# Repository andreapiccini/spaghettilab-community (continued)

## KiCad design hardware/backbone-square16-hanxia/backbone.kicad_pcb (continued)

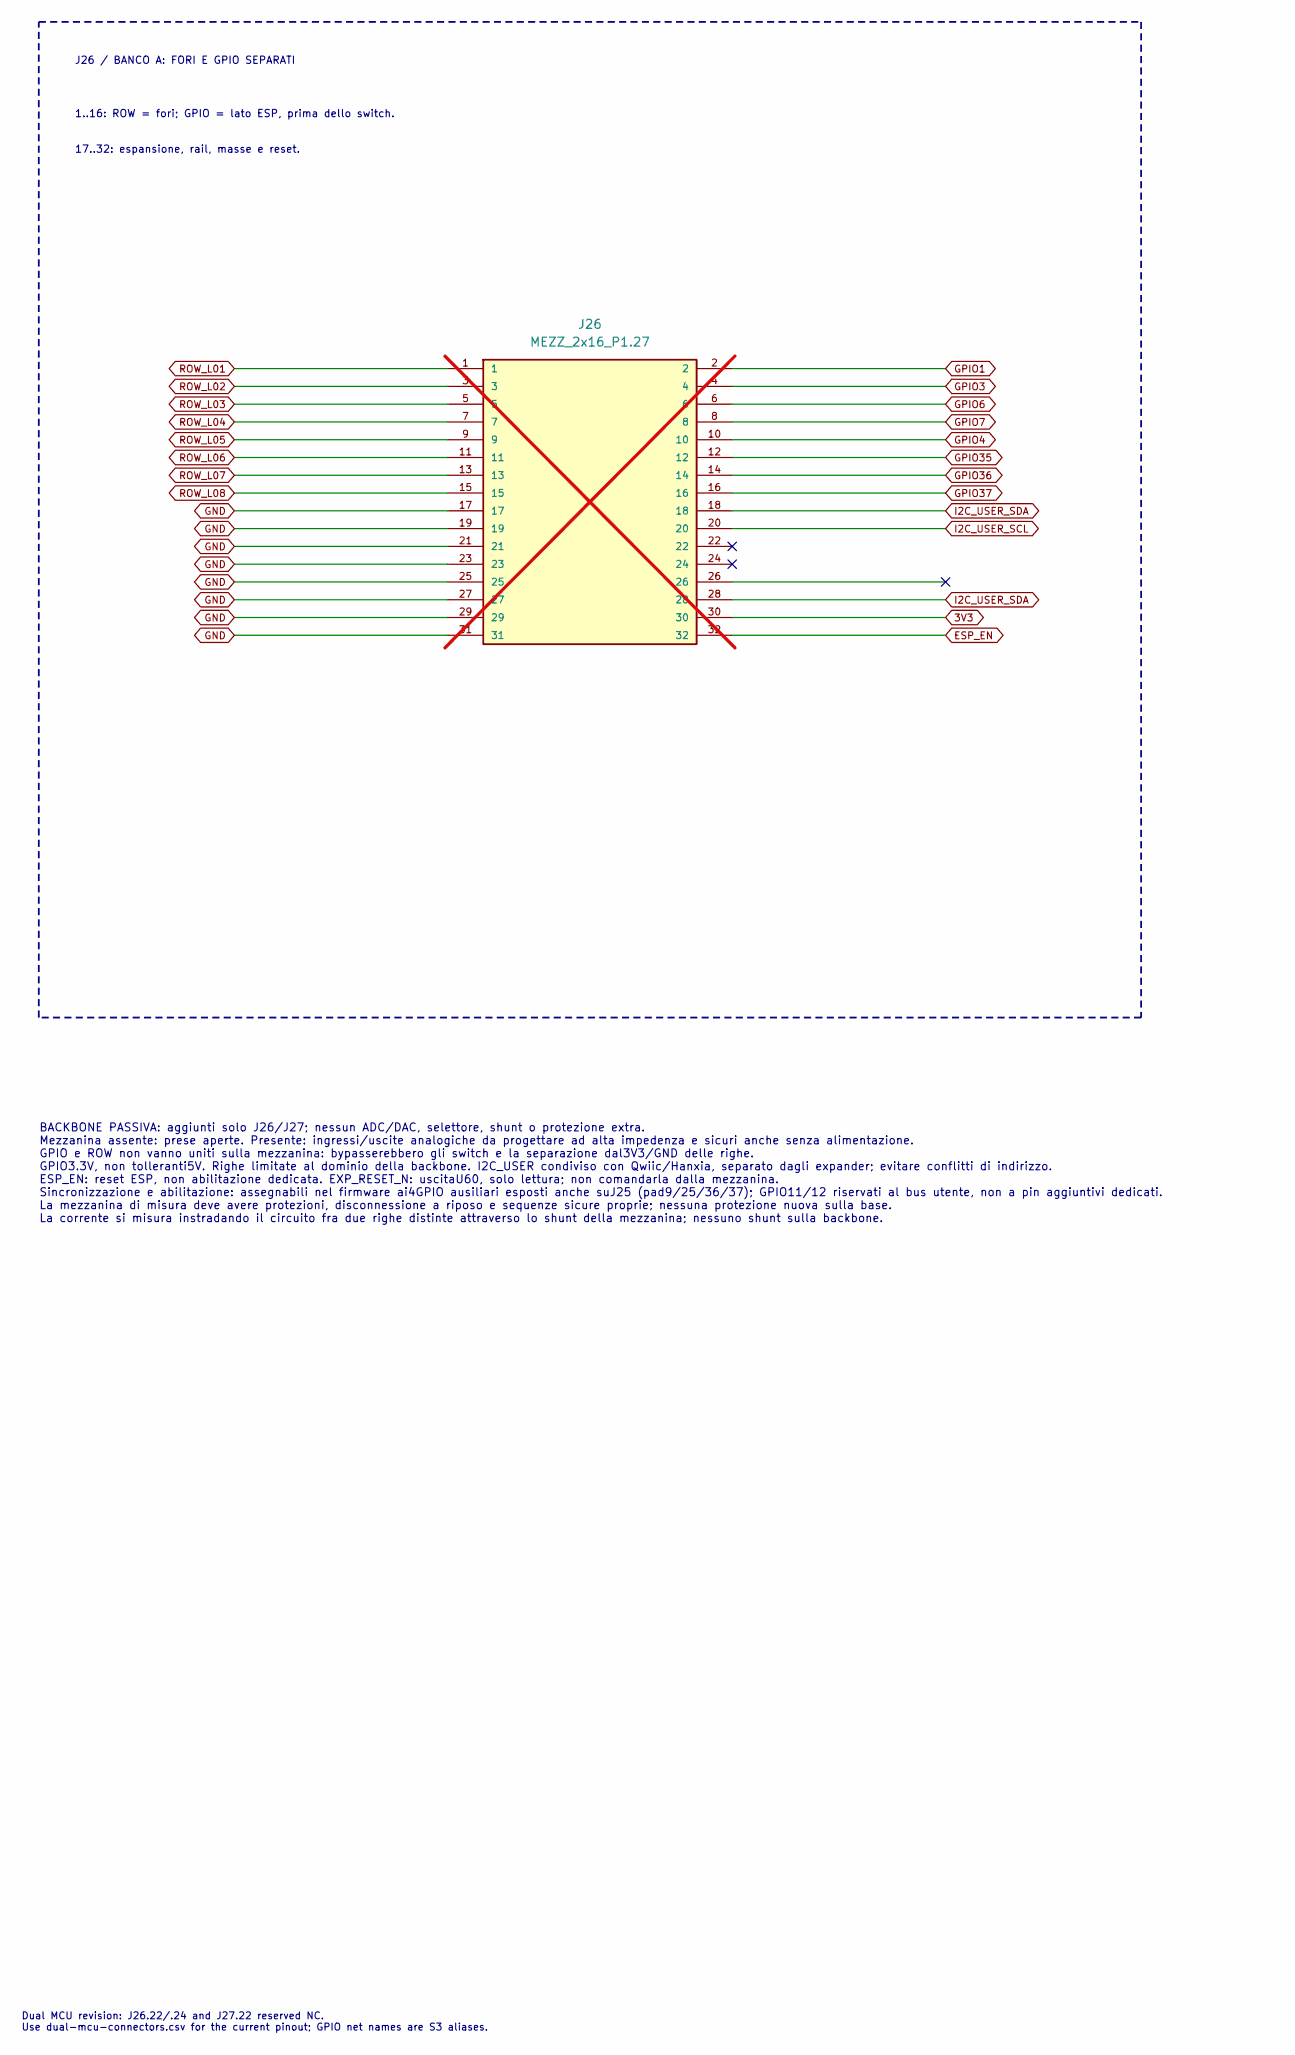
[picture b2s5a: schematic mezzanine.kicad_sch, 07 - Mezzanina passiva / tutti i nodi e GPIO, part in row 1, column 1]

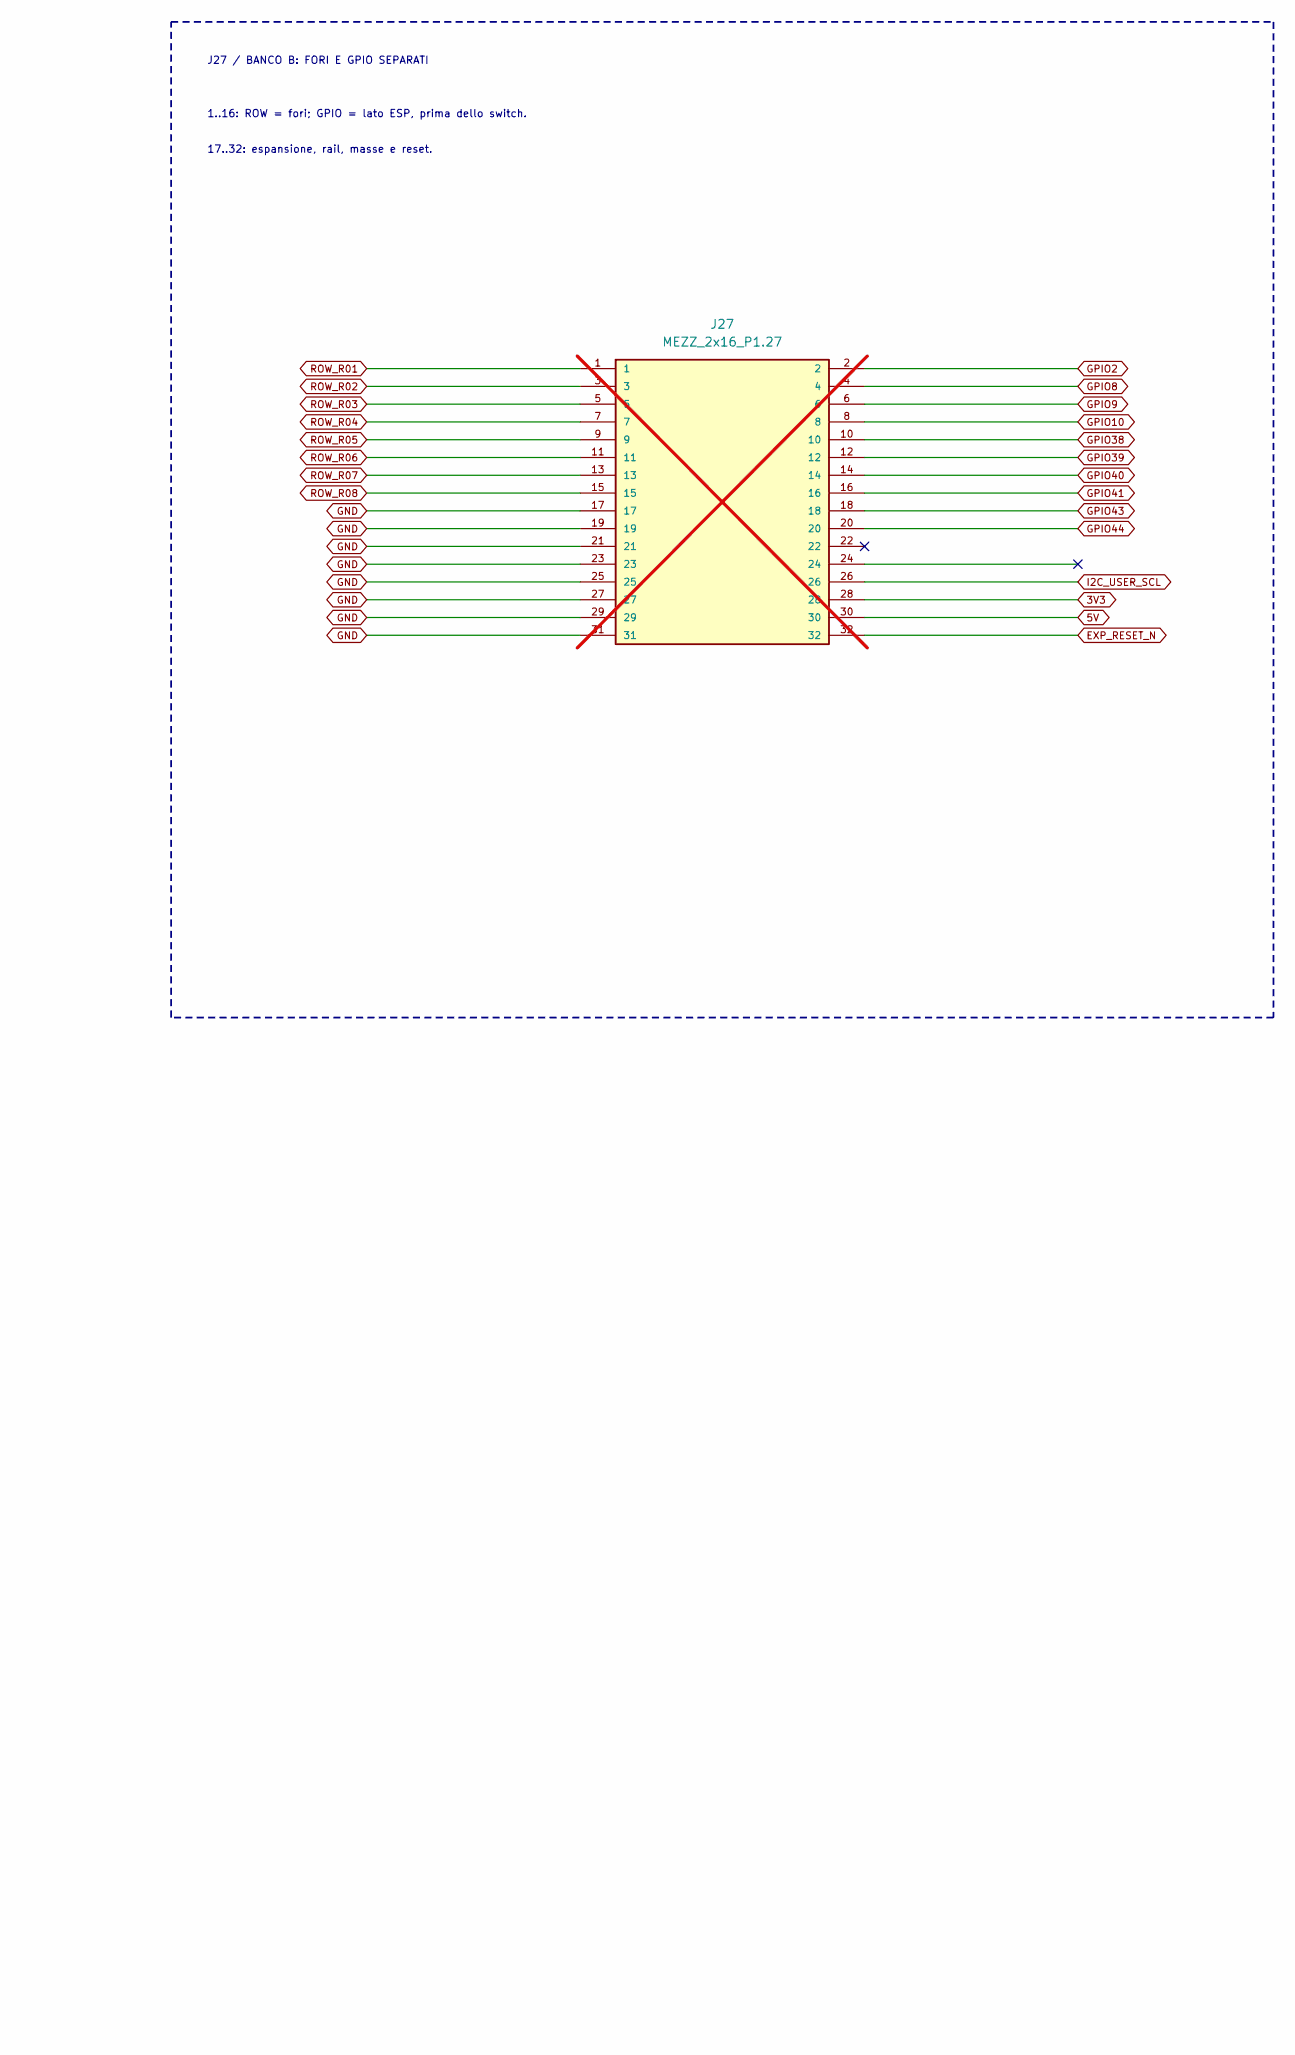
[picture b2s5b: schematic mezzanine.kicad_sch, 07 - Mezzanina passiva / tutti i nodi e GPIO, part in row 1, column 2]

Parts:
J26, J27: MEZZ_2x16_P1.27; PinSocket_2x16_P1.27mm_Vertical; not fitted

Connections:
3V3: J26.30, J27.28; also elsewhere on the board
5V: J27.30; also elsewhere on the board
ESP_EN: J26.32; also elsewhere on the board
EXP_RESET_N: J27.32; also elsewhere on the board
GND: J26.17, J26.19, J26.21, J26.23, J26.25, J26.27, J26.29, J26.31, J27.17, J27.19, J27.21, J27.23, J27.25, J27.27, J27.29, J27.31; also elsewhere on the board
GPIO1: J26.2; also elsewhere on the board
GPIO2: J27.2; also elsewhere on the board
GPIO3: J26.4; also elsewhere on the board
GPIO4: J26.10; also elsewhere on the board
GPIO6: J26.6; also elsewhere on the board
GPIO7: J26.8; also elsewhere on the board
GPIO8: J27.4; also elsewhere on the board
GPIO9: J27.6; also elsewhere on the board
GPIO10: J27.8; also elsewhere on the board
GPIO35: J26.12; also elsewhere on the board
GPIO36: J26.14; also elsewhere on the board
GPIO37: J26.16; also elsewhere on the board
GPIO38: J27.10; also elsewhere on the board
GPIO39: J27.12; also elsewhere on the board
GPIO40: J27.14; also elsewhere on the board
GPIO41: J27.16; also elsewhere on the board
GPIO43: J27.18; also elsewhere on the board
GPIO44: J27.20; also elsewhere on the board
I2C_USER_SCL: J26.20, J27.26; also elsewhere on the board
I2C_USER_SDA: J26.18, J26.28; also elsewhere on the board
ROW_L01: J26.1; also elsewhere on the board
ROW_L02: J26.3; also elsewhere on the board
ROW_L03: J26.5; also elsewhere on the board
ROW_L04: J26.7; also elsewhere on the board
ROW_L05: J26.9; also elsewhere on the board
ROW_L06: J26.11; also elsewhere on the board
ROW_L07: J26.13; also elsewhere on the board
ROW_L08: J26.15; also elsewhere on the board
ROW_R01: J27.1; also elsewhere on the board
ROW_R02: J27.3; also elsewhere on the board
ROW_R03: J27.5; also elsewhere on the board
ROW_R04: J27.7; also elsewhere on the board
ROW_R05: J27.9; also elsewhere on the board
ROW_R06: J27.11; also elsewhere on the board
ROW_R07: J27.13; also elsewhere on the board
ROW_R08: J27.15; also elsewhere on the board

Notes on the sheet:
J26 / BANCO A: FORI E GPIO SEPARATI
1..16: ROW = fori; GPIO = lato ESP, prima dello switch.
17..32: espansione, rail, masse e reset.
J27 / BANCO B: FORI E GPIO SEPARATI
BACKBONE PASSIVA: aggiunti solo J26/J27; nessun ADC/DAC, selettore, shunt o protezione extra. Mezzanina assente: prese aperte. Presente: ingressi/uscite analogiche da progettare ad alta impedenza e sicuri anche senza alimentazione. GPIO e ROW non vanno uniti sulla mezzanina: bypasserebbero gli swit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
Dual MCU revision: J26.22/.24 and J27.22 reserved NC. Use dual-mcu-connectors.csv for the current pinout; GPIO net names are S3 aliases.

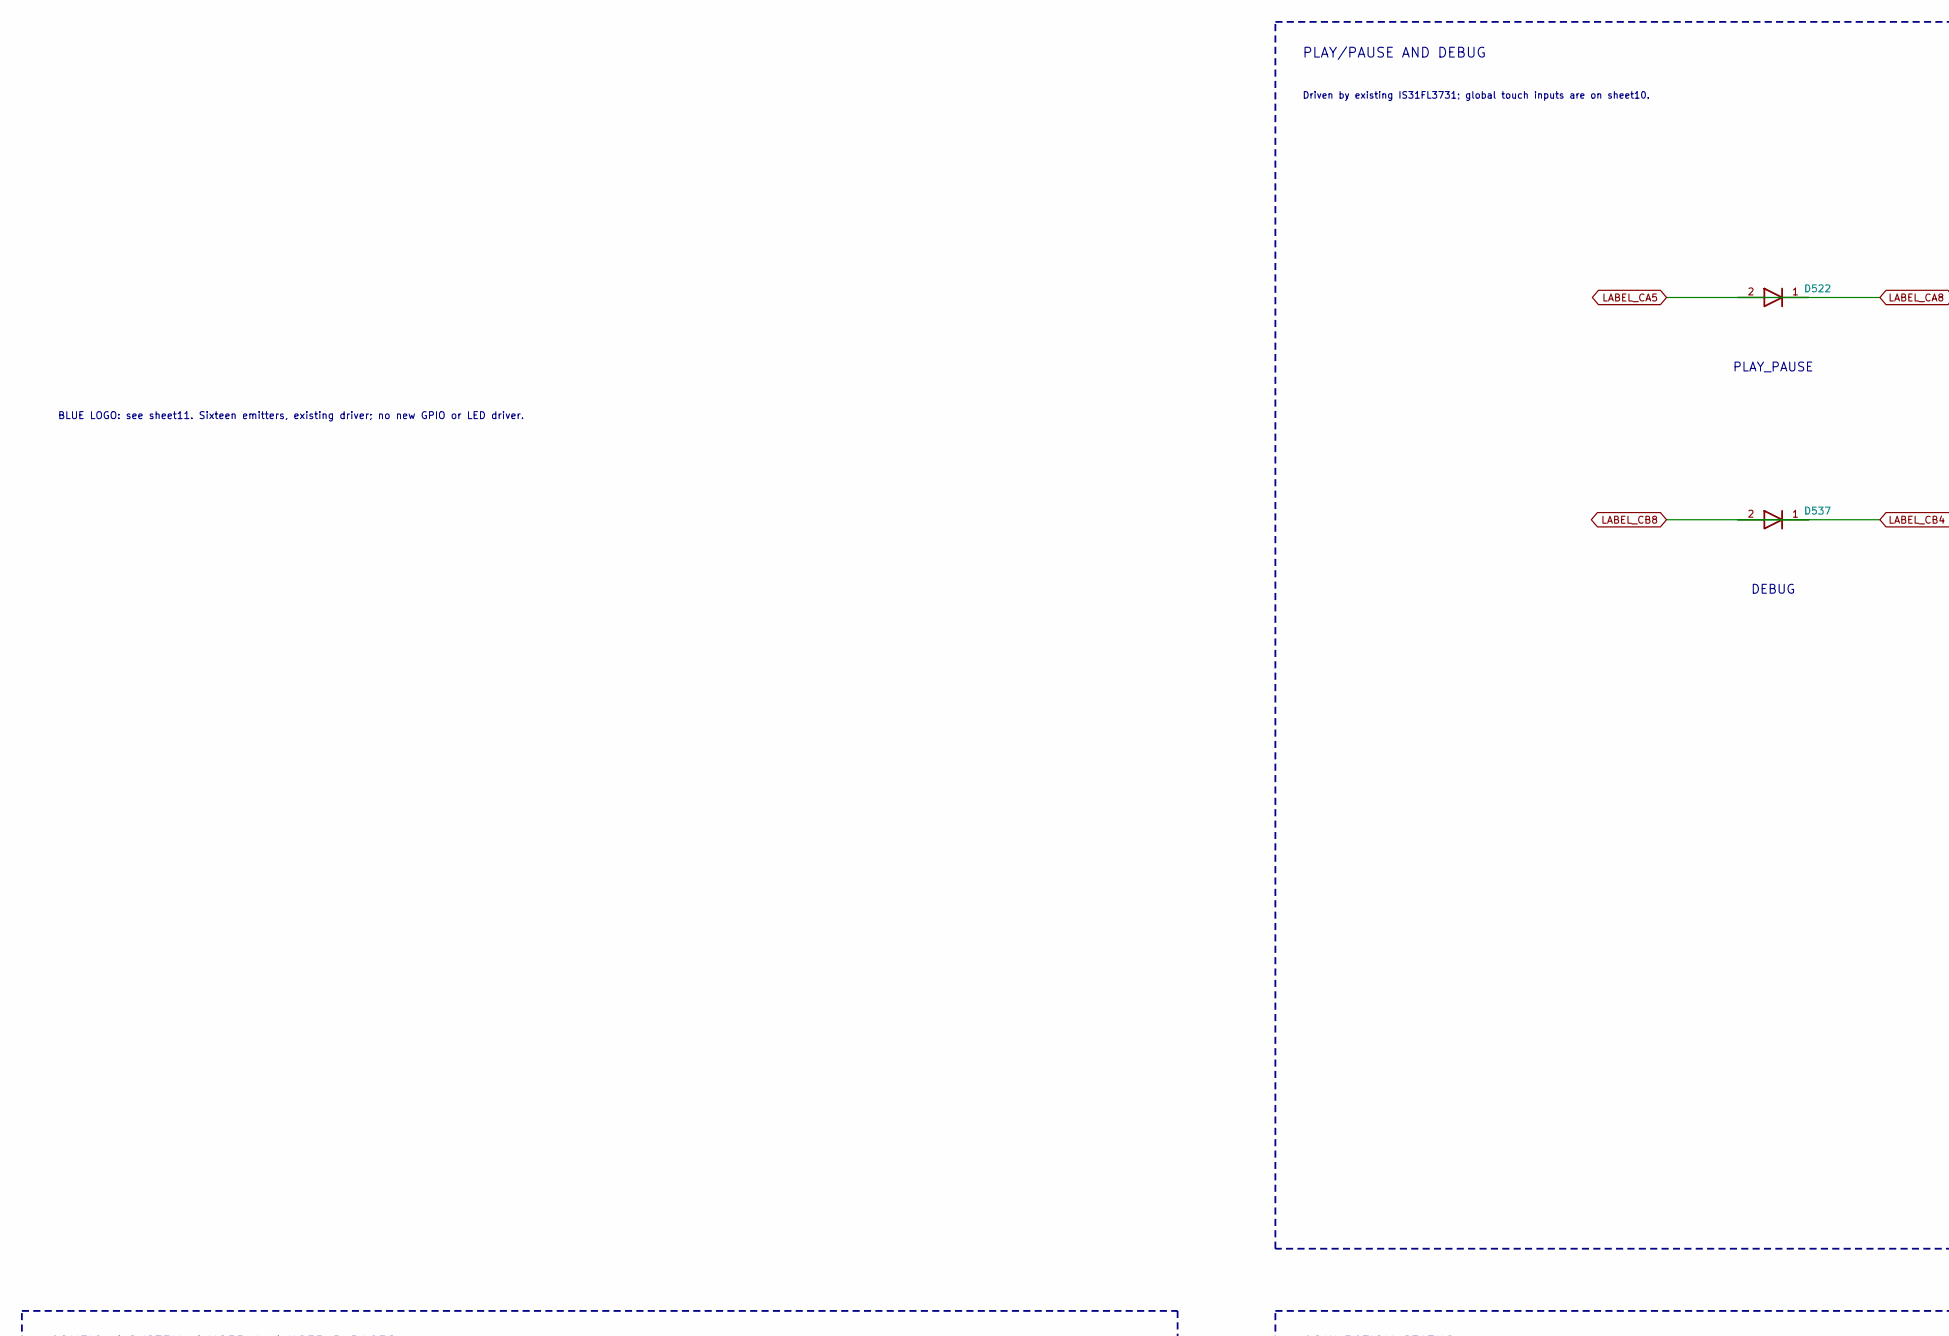
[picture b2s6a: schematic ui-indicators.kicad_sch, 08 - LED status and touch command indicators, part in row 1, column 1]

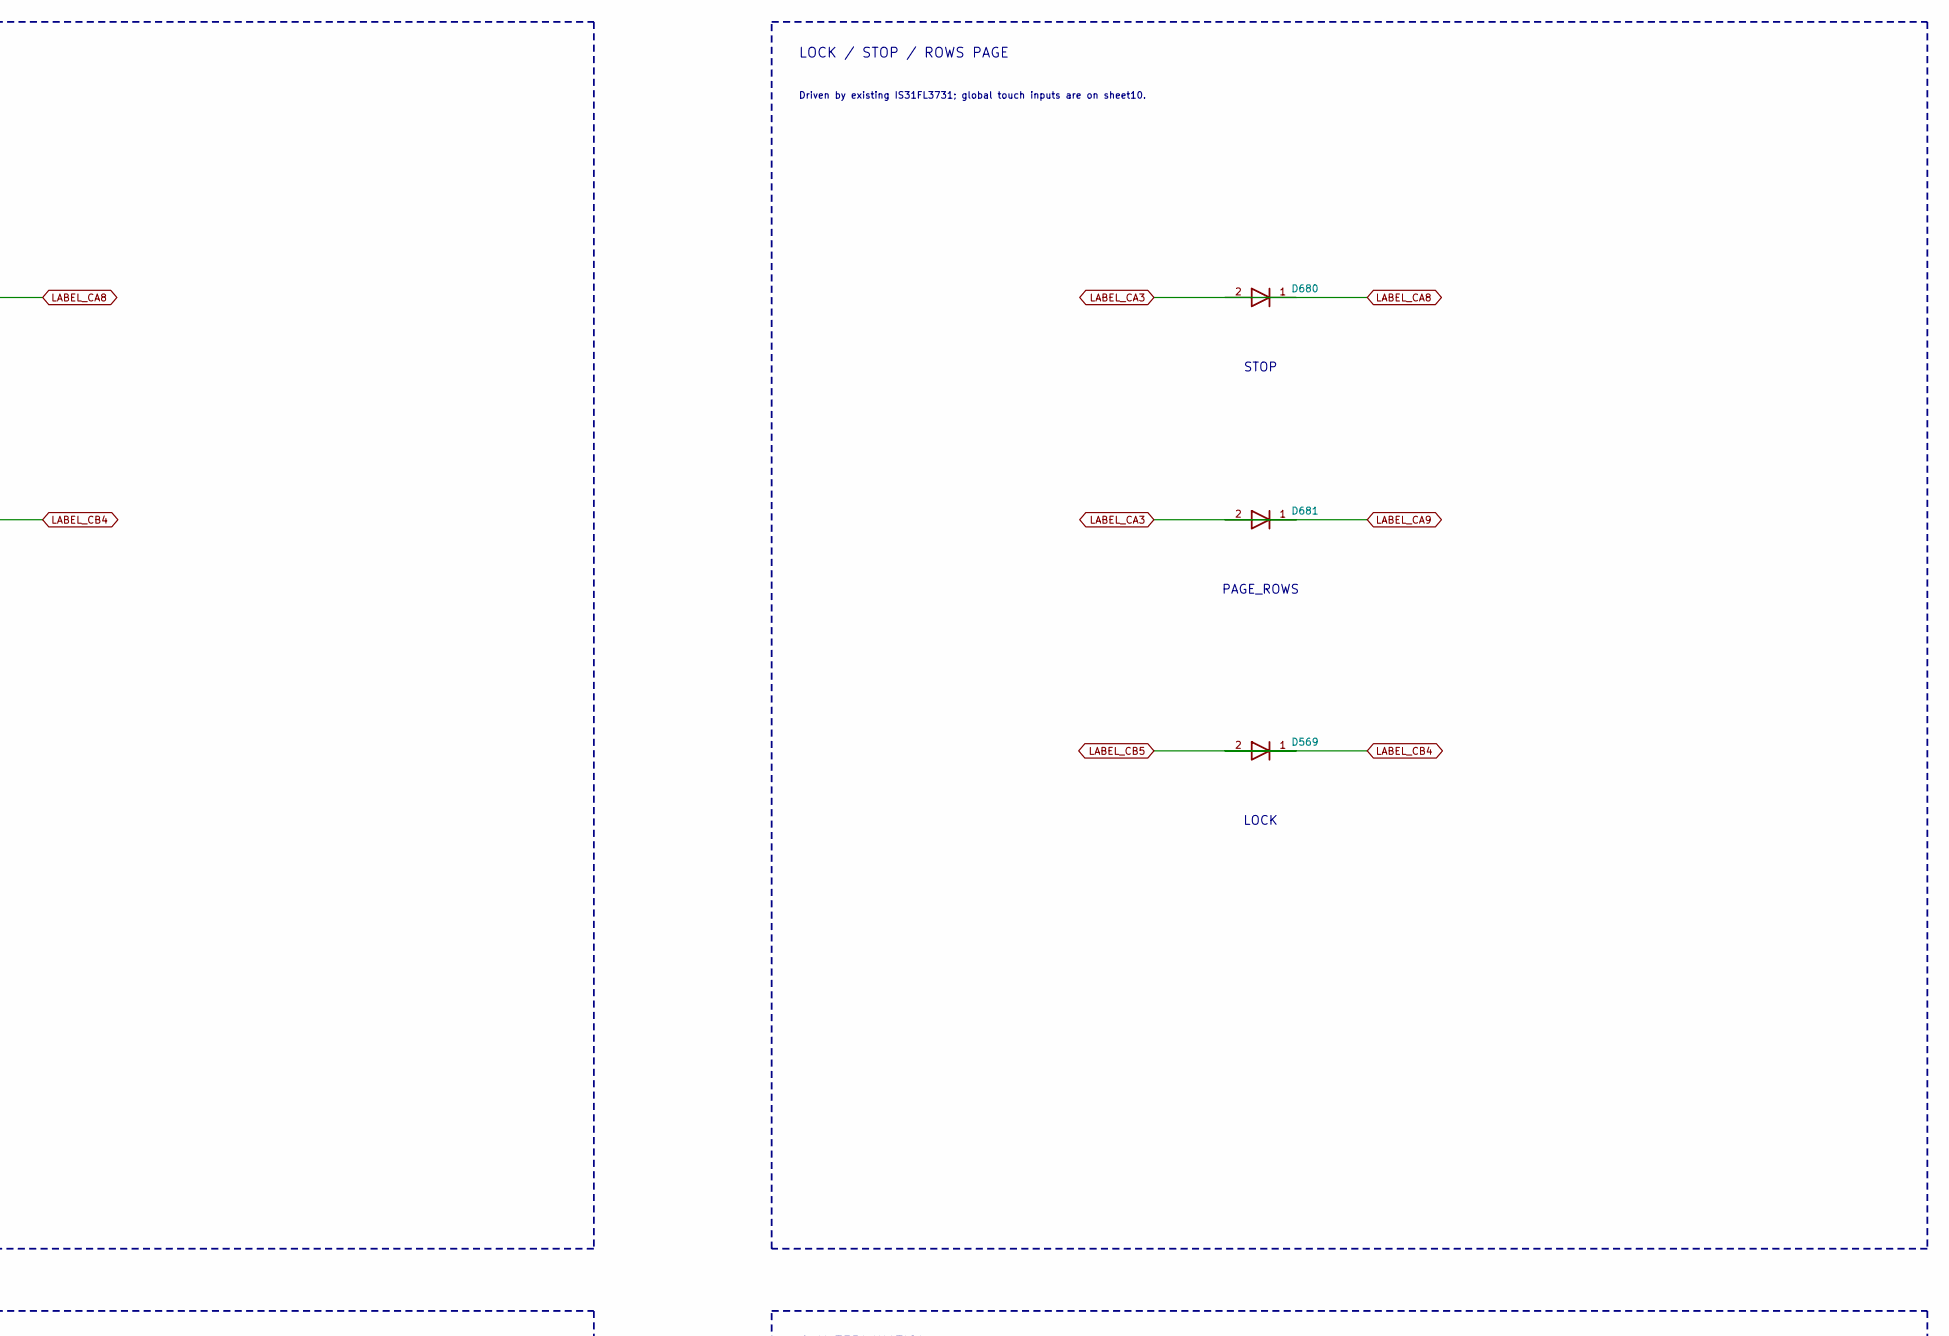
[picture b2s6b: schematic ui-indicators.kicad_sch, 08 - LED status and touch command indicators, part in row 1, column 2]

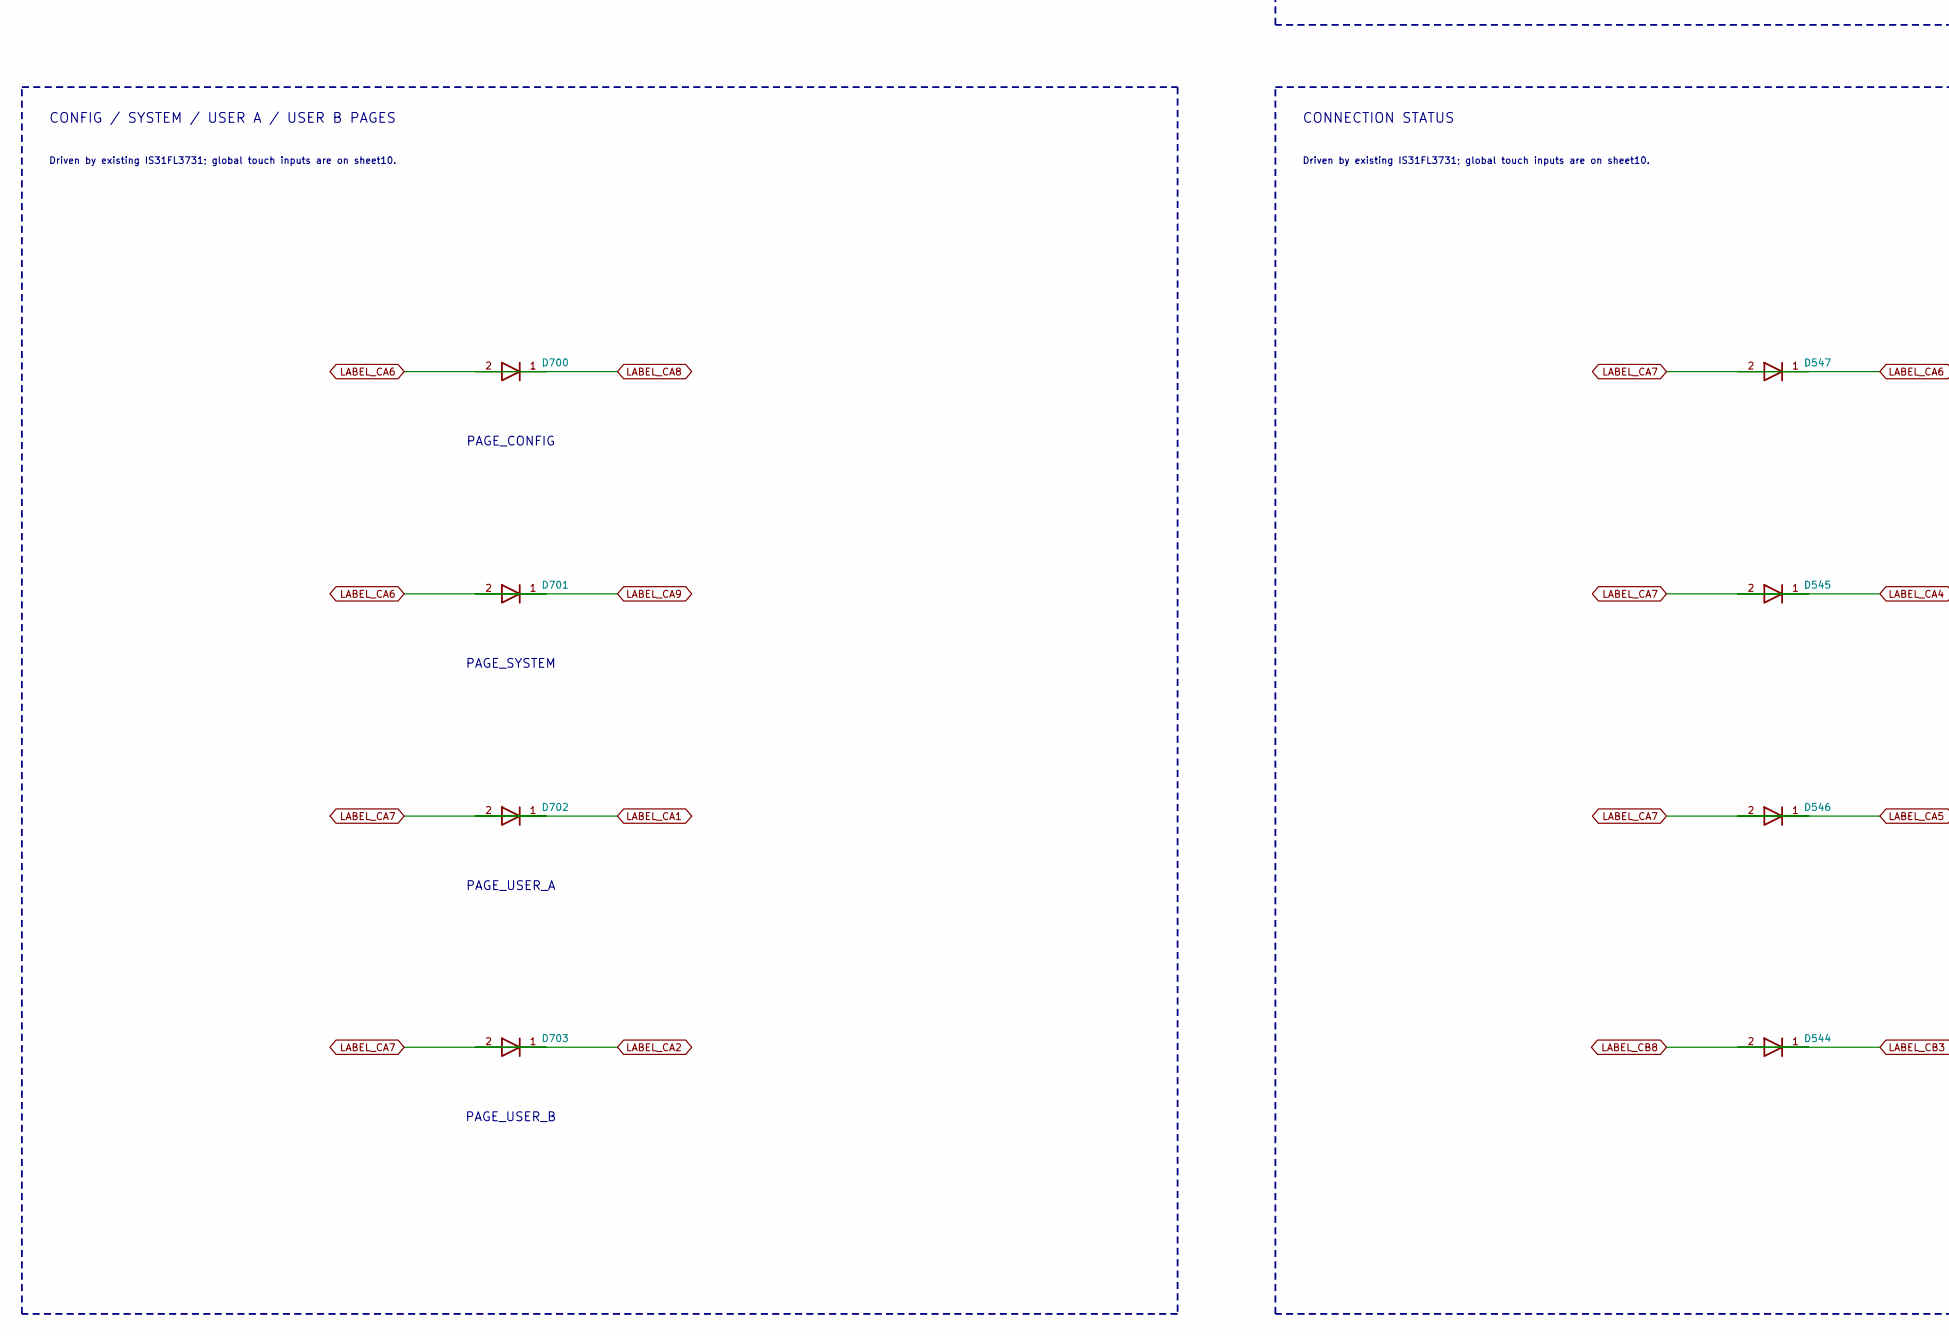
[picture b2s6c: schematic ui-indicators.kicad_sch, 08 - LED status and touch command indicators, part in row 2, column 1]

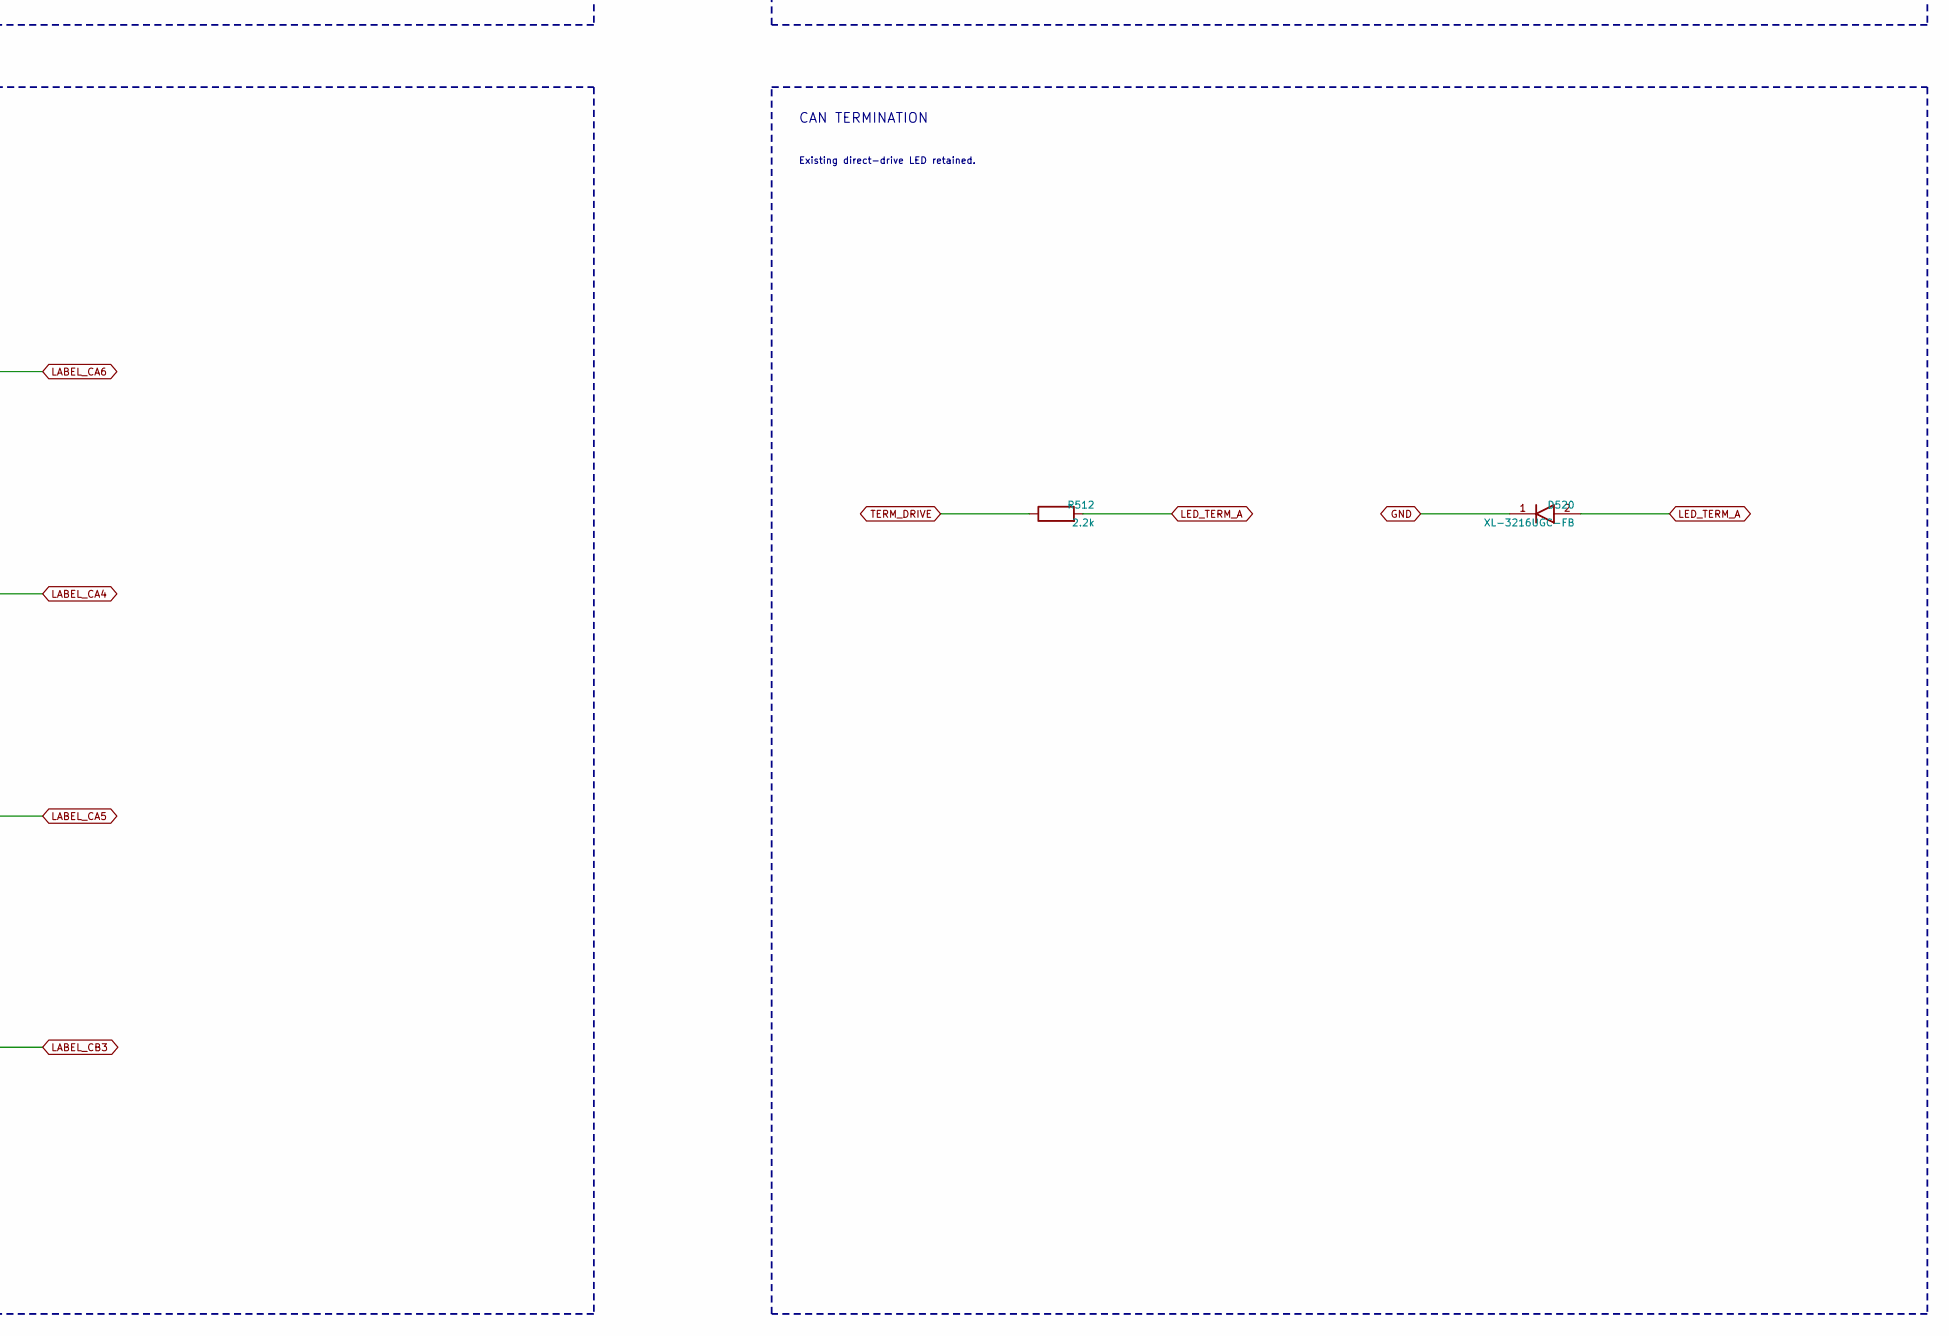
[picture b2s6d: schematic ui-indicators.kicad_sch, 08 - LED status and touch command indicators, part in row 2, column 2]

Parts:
D520, D522, D537, D544, D545: XL-3216UGC-FB; XINGLIGHT_XL3216_Reverse_Word_Window; MPN XL-3216UGC-FB; LCSC Part C3646937
D546, D547: XL-3216UBC-FB; XINGLIGHT_XL3216_Reverse_Word_Window; MPN XL-3216UBC-FB; LCSC Part C3646941
D569: XL-3216SURC-FB; XINGLIGHT_XL3216_Reverse_Word_Window; MPN XL-3216SURC-FB; LCSC Part C3646938
D680, D700, D701, D702, D703: XL-3216UGC-FB; XINGLIGHT_XL3216_Reverse_Word_Window
D681: XL-3216UBC-FB; XINGLIGHT_XL3216_Reverse_Word_Window
R512: 2.2k; R_0603_1608Metric; MPN 0603WAF2201T5E; LCSC Part C4190

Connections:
GND: D520.1 (K); also elsewhere on the board
LABEL_CA1: D702.2 (A); also elsewhere on the board
LABEL_CA2: D703.2 (A); also elsewhere on the board
LABEL_CA3: D680.1 (K), D681.1 (K); also elsewhere on the board
LABEL_CA4: D545.2 (A); also elsewhere on the board
LABEL_CA5: D522.1 (K), D546.2 (A); also elsewhere on the board
LABEL_CA6: D547.2 (A), D700.1 (K), D701.1 (K); also elsewhere on the board
LABEL_CA7: D545.1 (K), D546.1 (K), D547.1 (K), D702.1 (K), D703.1 (K); also elsewhere on the board
LABEL_CA8: D522.2 (A), D680.2 (A), D700.2 (A); also elsewhere on the board
LABEL_CA9: D681.2 (A), D701.2 (A); also elsewhere on the board
LABEL_CB3: D544.2 (A); also elsewhere on the board
LABEL_CB4: D537.2 (A), D569.2 (A); also elsewhere on the board
LABEL_CB5: D569.1 (K); also elsewhere on the board
LABEL_CB8: D537.1 (K), D544.1 (K); also elsewhere on the board
LED_TERM_A: D520.2 (A), R512.2
TERM_DRIVE: R512.1; also elsewhere on the board

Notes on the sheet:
PLAY/PAUSE AND DEBUG
Driven by existing IS31FL3731; global touch inputs are on sheet10.
LOCK / STOP / ROWS PAGE
CONFIG / SYSTEM / USER A / USER B PAGES
CONNECTION STATUS
CAN TERMINATION
Existing direct-drive LED retained.
BLUE LOGO: see sheet11. Sixteen emitters, existing driver; no new GPIO or LED driver.
PLAY_PAUSE
DEBUG
STOP
PAGE_ROWS
LOCK
PAGE_CONFIG
PAGE_SYSTEM
PAGE_USER_A
PAGE_USER_B

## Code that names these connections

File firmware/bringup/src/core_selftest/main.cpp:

#include <Arduino.h>
#include <WiFi.h>
#include <BLEDevice.h>
#include <BLEServer.h>
#include <esp_chip_info.h>
#include <esp_flash.h>
#include <esp_mac.h>

#include "sk6812_rmt.h"

// Pin map from hardware/core/core.kicad_sch + core.kicad_pcb (U19 ESP32-S3-MINI-1).
// USB_D+/D- = GPIO20/19 (native CDC). LED_DATA = GPIO34 via SN74AHCT1G14 (invert!).
// CAN: GPIO5 = CORE_CAN_TX -> SN65HVD230 D, GPIO4 = CORE_CAN_RX <- R (local echo).
// SW2 BOOT = GPIO0. PROG J17 = GPIO43 TX / GPIO44 RX. Link Bay J8 = GPIO35..42,45..48.

static const int kLedGpio = 34;
static const int kCanRx = 4;
static const int kCanTx = 5;
static const int kBoot = 0;
static const int kBayGpios[] = {35, 36, 37, 38, 39, 40, 41, 42, 45, 46, 47, 48};

static bool s_ble_ok = false;

static void banner() {
    Serial.println();
    Serial.println("================================================");
    Serial.println("  SpaghettiLAB CORE  ESP32-S3 self-test");
    Serial.println("  Schematic: hardware/core/core.kicad_sch");
    Serial.println("================================================");
    Serial.println("Commands:  a=all  r=rgb  c=can  w=wifi  b=ble  g=gpio  h=help");
}

static void test_chip() {
    Serial.println();
    Serial.println("[1] Chip / flash / USB");
    Serial.printf("    model     %s  rev %d  cores %d\n", ESP.getChipModel(), ESP.getChipRevision(), ESP.getChipCores());
    Serial.printf("    CPU       %u MHz\n", ESP.getCpuFreqMHz());
    Serial.printf("    flash     %u KB\n", ESP.getFlashChipSize() / 1024);
    Serial.printf("    PSRAM     %u KB\n", ESP.getPsramSize() / 1024);
    Serial.printf("    heap      %u free / %u min\n", ESP.getFreeHeap(), ESP.getMinFreeHeap());
    uint8_t mac[6] = {};
    esp_read_mac(mac, ESP_MAC_WIFI_STA);
    Serial.printf("    Wi-Fi MAC %02X:%02X:%02X:%02X:%02X:%02X\n", mac[0], mac[1], mac[2], mac[3], mac[4], mac[5]);
    Serial.println("    USB CDC   PASS  (you are reading this)");
}

static void test_rgb() {
    Serial.println();
    Serial.println("[2] SK6812 on GPIO34 (inverter U10 — look at the CORE LED)");
    const uint8_t colors[][3] = {{48, 0, 0}, {0, 48, 0}, {0, 0, 48}, {48, 48, 48}, {0, 0, 0}};
    const char *names[] = {"RED", "GREEN", "BLUE", "WHITE", "OFF"};
    for (int i = 0; i < 5; ++i) {
        sk6812_fill(colors[i][0], colors[i][1], colors[i][2]);
        sk6812_show();
        Serial.printf("    %s\n", names[i]);
        delay(400);
    }
    Serial.println("    PASS if the on-board ARGB stepped through those colors");
}

static void test_boot() {
    pinMode(kBoot, INPUT_PULLUP);
    const int level = digitalRead(kBoot);
    Serial.println();
    Serial.println("[3] BOOT SW2 on GPIO0");
    Serial.printf("    GPIO0 = %s  (released = HIGH, held = LOW)\n", level ? "HIGH" : "LOW");
}

static void test_can_echo() {
    Serial.println();
    Serial.println("[4] CAN PHY echo  GPIO5 TX -> SN65HVD230 -> GPIO4 RX");
    gpio_reset_pin((gpio_num_t)kCanTx);
    gpio_reset_pin((gpio_num_t)kCanRx);
    pinMode(kCanTx, OUTPUT);
    pinMode(kCanRx, INPUT);
    digitalWrite(kCanTx, HIGH);
    delay(5);
    const int rec = digitalRead(kCanRx);
    digitalWrite(kCanTx, LOW);
    delay(5);
    const int dom = digitalRead(kCanRx);
    digitalWrite(kCanTx, HIGH);
    delay(5);
    const int rec2 = digitalRead(kCanRx);
    const bool ok = rec == HIGH && rec2 == HIGH;
    Serial.printf("    TX recessive HIGH -> RX=%s\n", rec ? "HIGH" : "LOW");
    Serial.printf("    TX dominant  LOW  -> RX=%s  (local echo often stays HIGH if bus is open)\n",
                  dom ? "HIGH" : "LOW");
    Serial.printf("    TX recessive HIGH -> RX=%s\n", rec2 ? "HIGH" : "LOW");
    if (ok) {
        Serial.println("    PASS  transceiver is driving RX (idle/recessive seen)");
    } else {
        Serial.println("    FAIL  GPIO4 did not follow recessive HIGH — check U21 / 3V3 / CAN wiring");
    }
    if (dom == LOW) {
        Serial.println("    note: dominant echoed — bus or terminator is loading the pair");
    }
}

static void test_wifi() {
    Serial.println();
    Serial.println("[5] Wi-Fi scan");
    WiFi.mode(WIFI_STA);
    WiFi.disconnect(true, true);
    delay(80);
    const int n = WiFi.scanNetworks(/*async=*/false, /*hidden=*/true);
    if (n < 0) {
        Serial.println("    FAIL  scan error");
        return;
    }
    Serial.printf("    found %d AP(s)\n", n);
    for (int i = 0; i < n && i < 8; ++i) {
        Serial.printf("      %s  ch %d  %d dBm\n", WiFi.SSID(i).c_str(), WiFi.channel(i), WiFi.RSSI(i));
    }
    Serial.println(n > 0 ? "    PASS" : "    WARN  no APs (radio may still be OK)");
    WiFi.scanDelete();
    WiFi.mode(WIFI_OFF);
}

static void test_ble() {
    Serial.println();
    Serial.println("[6] BLE advertise  'SL-CORE-TEST'");
    if (!s_ble_ok) {
        BLEDevice::init("SL-CORE-TEST");
        BLEServer *server = BLEDevice::createServer();
        (void)server;
        BLEAdvertising *adv = BLEDevice::getAdvertising();
        adv->setScanResponse(true);
        adv->start();
        s_ble_ok = true;
    }
    Serial.println("    PASS  advertising (scan with a phone)");
}

static void test_bay_gpio() {
    Serial.println();
    Serial.println("[7] Link Bay J8 GPIOs (INPUT_PULLUP)");
    for (int gpio : kBayGpios) {
        pinMode(gpio, INPUT_PULLUP);
        delayMicroseconds(50);
        const int v = digitalRead(gpio);
        Serial.printf("    GPIO%02d  %s\n", gpio, v ? "HIGH" : "LOW ");
    }
    Serial.println("    floating pins should read HIGH; a short to GND reads LOW");
}

static void run_all() {
    test_chip();
    test_rgb();
    test_boot();
    test_can_echo();
    test_wifi();
    test_ble();
    test_bay_gpio();
    Serial.println();
    Serial.println("Done. RGB returns to slow cycle. Type h for commands.");
}

void setup() {
    Serial.begin(115200);
    delay(400);
    sk6812_begin(kLedGpio, 1, /*invert_out=*/true);
    sk6812_fill(0, 0, 24);
    sk6812_show();
    banner();
    run_all();
}

void loop() {
    while (Serial.available()) {
        const int c = Serial.read();
        if (c == 'a' || c == 'A') run_all();
        else if (c == 'r' || c == 'R') test_rgb();
        else if (c == 'c' || c == 'C') test_can_echo();
        else if (c == 'w' || c == 'W') test_wifi();
        else if (c == 'b' || c == 'B') test_ble();
        else if (c == 'g' || c == 'G') test_bay_gpio();
        else if (c == 'h' || c == 'H' || c == '?') banner();
    }

    static uint32_t last = 0;
    const uint32_t now = millis();
    if (now - last >= 800) {
        last = now;
        const uint8_t phase = (now / 800) % 3;
        if (phase == 0) sk6812_fill(32, 0, 0);
        else if (phase == 1) sk6812_fill(0, 32, 0);
        else sk6812_fill(0, 0, 32);
        sk6812_show();
    }
}

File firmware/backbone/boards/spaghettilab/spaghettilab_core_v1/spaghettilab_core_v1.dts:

/dts-v1/;

#include <espressif/esp32c3/esp32c3_mini_n4.dtsi>
#include <espressif/partitions_0x0_default.dtsi>
#include <zephyr/dt-bindings/pinctrl/esp-pinctrl-common.h>
#include <zephyr/dt-bindings/pinctrl/esp32c3-pinctrl.h>
#include <zephyr/dt-bindings/pinctrl/esp32c3-gpio-sigmap.h>

/ {
	model = "Spaghetti LAB Core V1";
	compatible = "spaghettilab,core-v1", "espressif,esp32c3";

	chosen {
		zephyr,sram = &sram1;
		zephyr,console = &usb_serial;
		zephyr,shell-uart = &usb_serial;
		zephyr,flash = &flash0;
		zephyr,code-partition = &slot0_partition;
		zephyr,uart-mcumgr = &uart1;
		zephyr,bt-hci = &esp32_bt_hci;
	};

	aliases {
		i2c-0 = &i2c0;
	};

	spaghetti_ports {
		compatible = "simple-bus";
		#address-cells = <1>;
		#size-cells = <0>;

		port0: port@0 {
			compatible = "spaghettilab,port";
			reg = <0>;
			i2c = <&i2c0>;
			status = "okay";
		};

		/*
		 * A second connector exposing five raw digital signal lines on
		 * ESP32-C3 SuperMini breakout pins 0, 1, 5, 6, 7 — every
		 * production pin reference here is the SuperMini's own labeled
		 * breakout pin, chosen deliberately excluding the pins already
		 * wired above (GPIO3/GPIO4, I2C0) and GPIO2/GPIO8/GPIO9 (ESP32-C3
		 * strapping pins, sampled by the boot ROM at reset to select
		 * flash voltage/download mode — safe to use as GPIO once running,
		 * but risky to wire to anything that could hold them low across a
		 * reset). Each line is both an input-gpios and output-gpios entry
		 * at the same signal index: the physical pin is bidirectional,
		 * which direction is actually used is a Module driver's own
		 * choice (its declared required_capabilities), not fixed here.
		 */
		port1: port@1 {
			compatible = "spaghettilab,port";
			reg = <1>;
			input-gpios = <&gpio0 0 GPIO_ACTIVE_HIGH>,
				      <&gpio0 1 GPIO_ACTIVE_HIGH>,
				      <&gpio0 5 GPIO_ACTIVE_HIGH>,
				      <&gpio0 6 GPIO_ACTIVE_HIGH>,
				      <&gpio0 7 GPIO_ACTIVE_HIGH>;
			output-gpios = <&gpio0 0 GPIO_ACTIVE_HIGH>,
				       <&gpio0 1 GPIO_ACTIVE_HIGH>,
				       <&gpio0 5 GPIO_ACTIVE_HIGH>,
				       <&gpio0 6 GPIO_ACTIVE_HIGH>,
				       <&gpio0 7 GPIO_ACTIVE_HIGH>;
			status = "okay";
		};
	};

	spaghetti_flows {
		compatible = "simple-bus";
		#address-cells = <1>;
		#size-cells = <0>;

		flow0: flow@0 {
			compatible = "spaghettilab,flow";
			reg = <0>;
			port = <&port0>;
			direction = "field-to-core";
			signal-count = <5>;
			function-bay-count = <0>;
			status = "okay";
		};

		flow1: flow@1 {
			compatible = "spaghettilab,flow";
			reg = <1>;
			port = <&port1>;
			direction = "bidirectional";
			signal-count = <5>;
			function-bay-count = <0>;
			status = "okay";
		};
	};

	maintenance_link0: maintenance-link {
		compatible = "spaghettilab,maintenance-link";
		normal-bus = <&i2c0>;
		maintenance-uart = <&uart1>;
		bootstrap-window-ms = <500>;
		status = "okay";
	};
};

&pinctrl {
	spaghetti_i2c0_default: spaghetti_i2c0_default {
		group1 {
			pinmux = <I2C0_SDA_GPIO3>, <I2C0_SCL_GPIO4>;
			bias-pull-up;
			drive-open-drain;
			output-high;
		};
	};

	spaghetti_uart1_maintenance: spaghetti_uart1_maintenance {
		group1 {
			pinmux = <UART1_RX_GPIO3>, <UART1_TX_GPIO4>;
		};
	};

	spaghetti_uart1_probe: spaghetti_uart1_probe {
		group1 {
			pinmux = <UART1_RX_GPIO3>;
			bias-pull-up;
		};
	};
};

&usb_serial {
	status = "okay";
};

&i2c0 {
	status = "okay";
	clock-frequency = <I2C_BITRATE_STANDARD>;
	pinctrl-0 = <&spaghetti_i2c0_default>;
	pinctrl-names = "default";
};

&uart1 {
	status = "okay";
	current-speed = <115200>;
	pinctrl-0 = <&spaghetti_uart1_probe>;
	pinctrl-1 = <&spaghetti_uart1_maintenance>;
	pinctrl-names = "default", "sleep";
};

&gpio0 {
	status = "okay";
};

&trng0 {
	status = "okay";
};

&wifi {
	status = "okay";
};

&esp32_bt_hci {
	status = "okay";
};
